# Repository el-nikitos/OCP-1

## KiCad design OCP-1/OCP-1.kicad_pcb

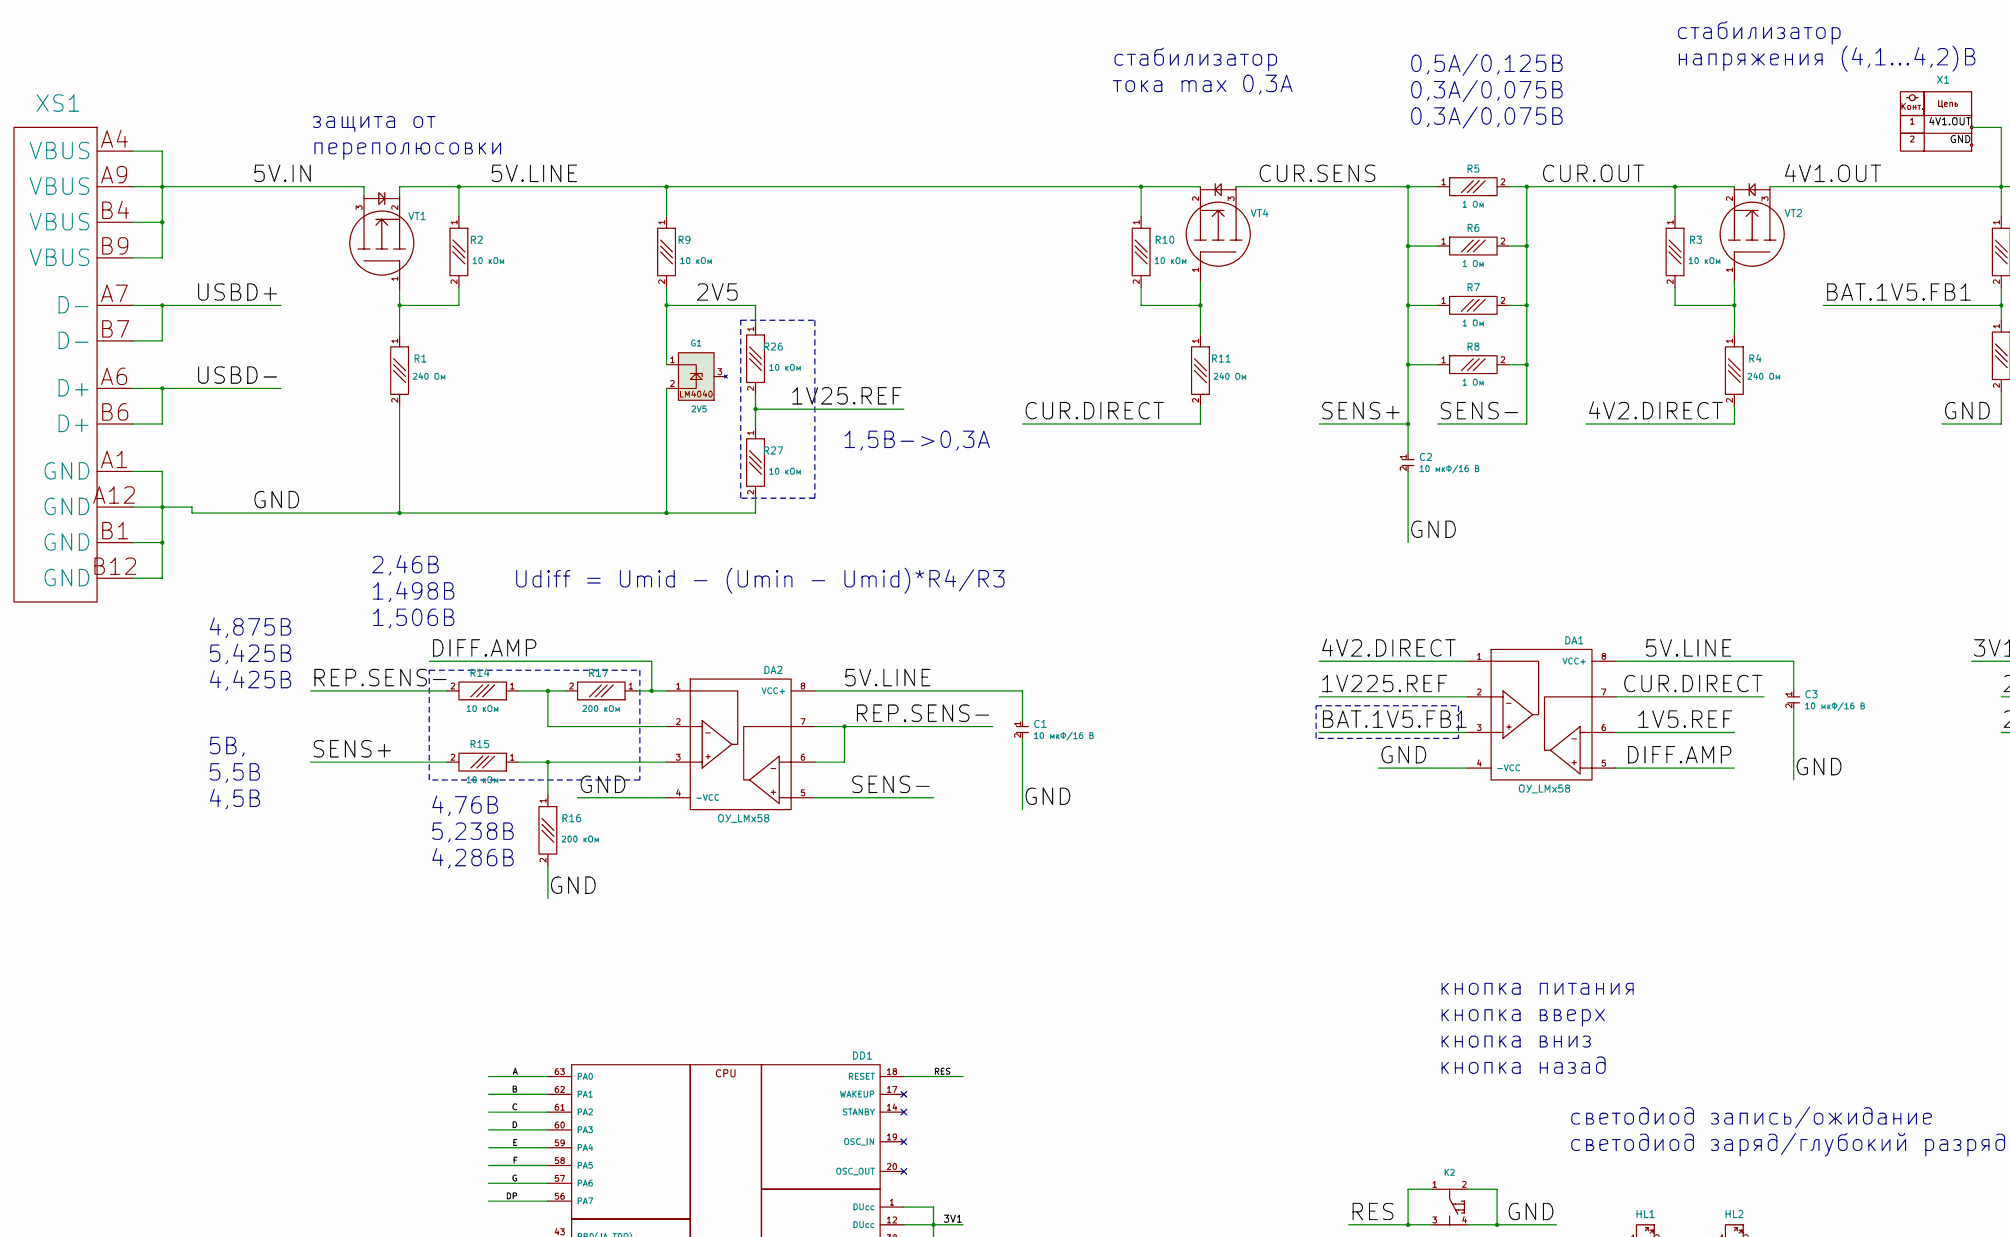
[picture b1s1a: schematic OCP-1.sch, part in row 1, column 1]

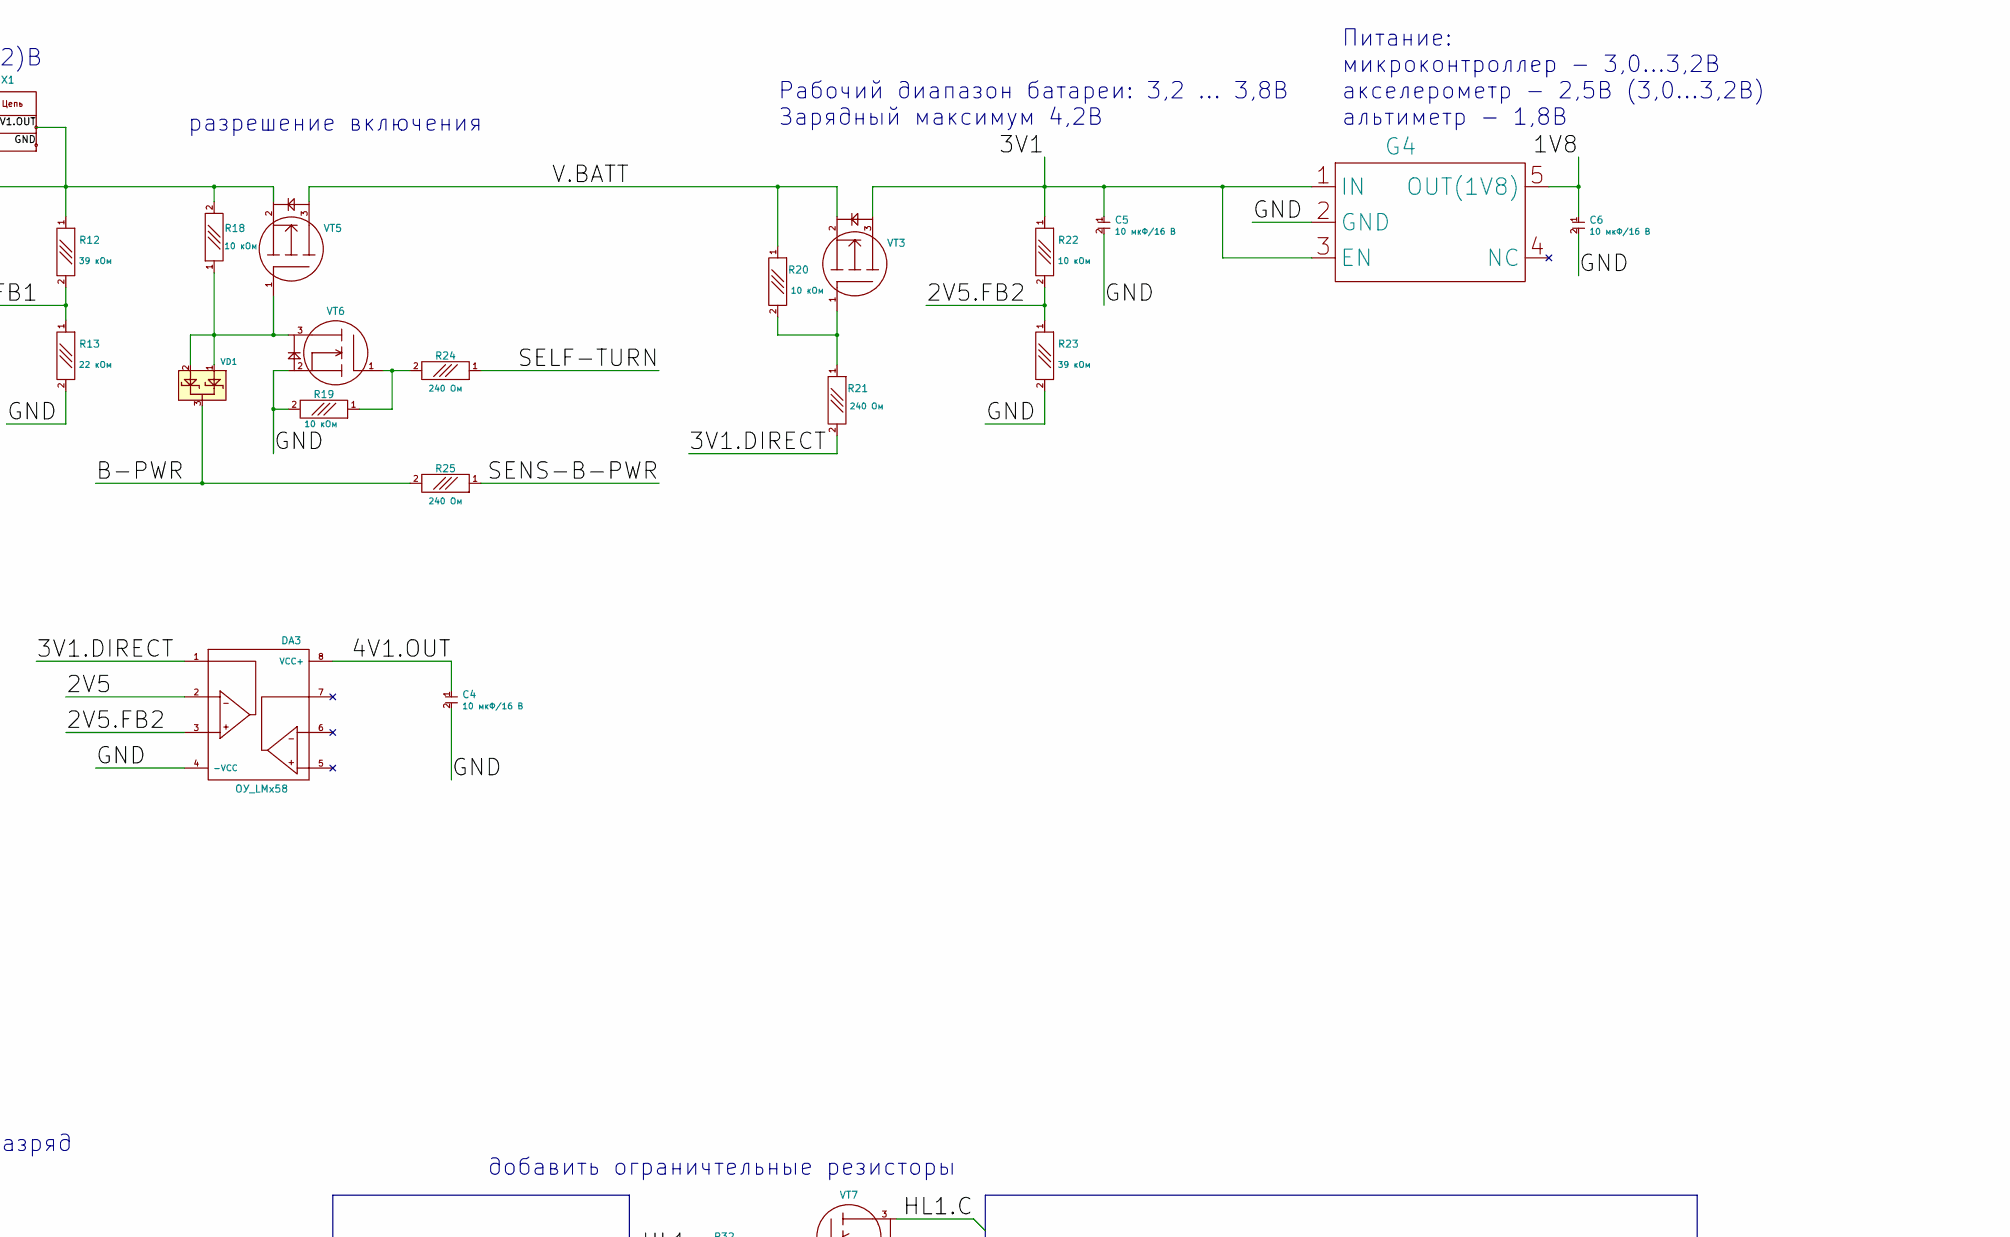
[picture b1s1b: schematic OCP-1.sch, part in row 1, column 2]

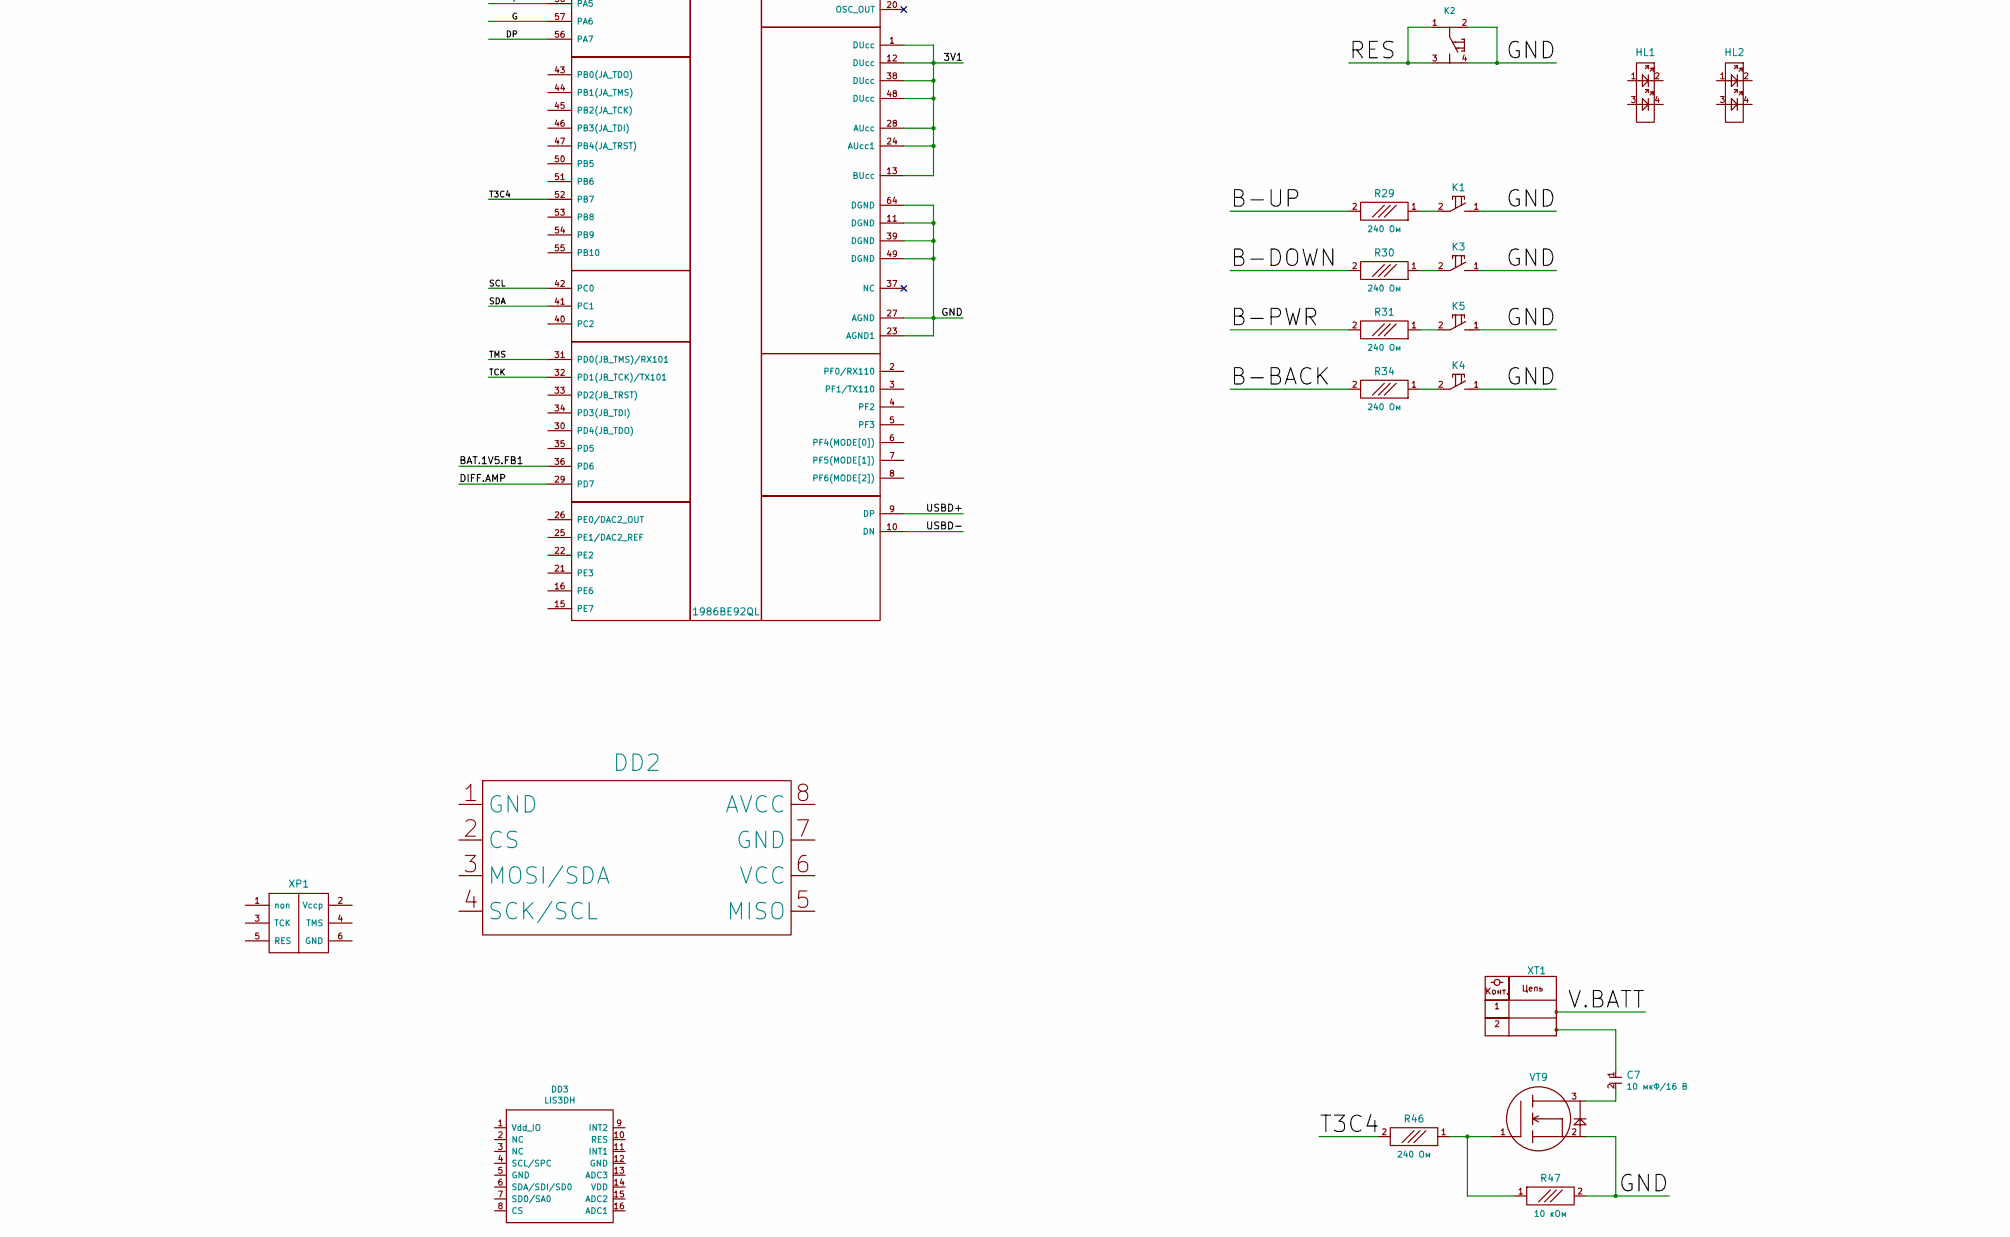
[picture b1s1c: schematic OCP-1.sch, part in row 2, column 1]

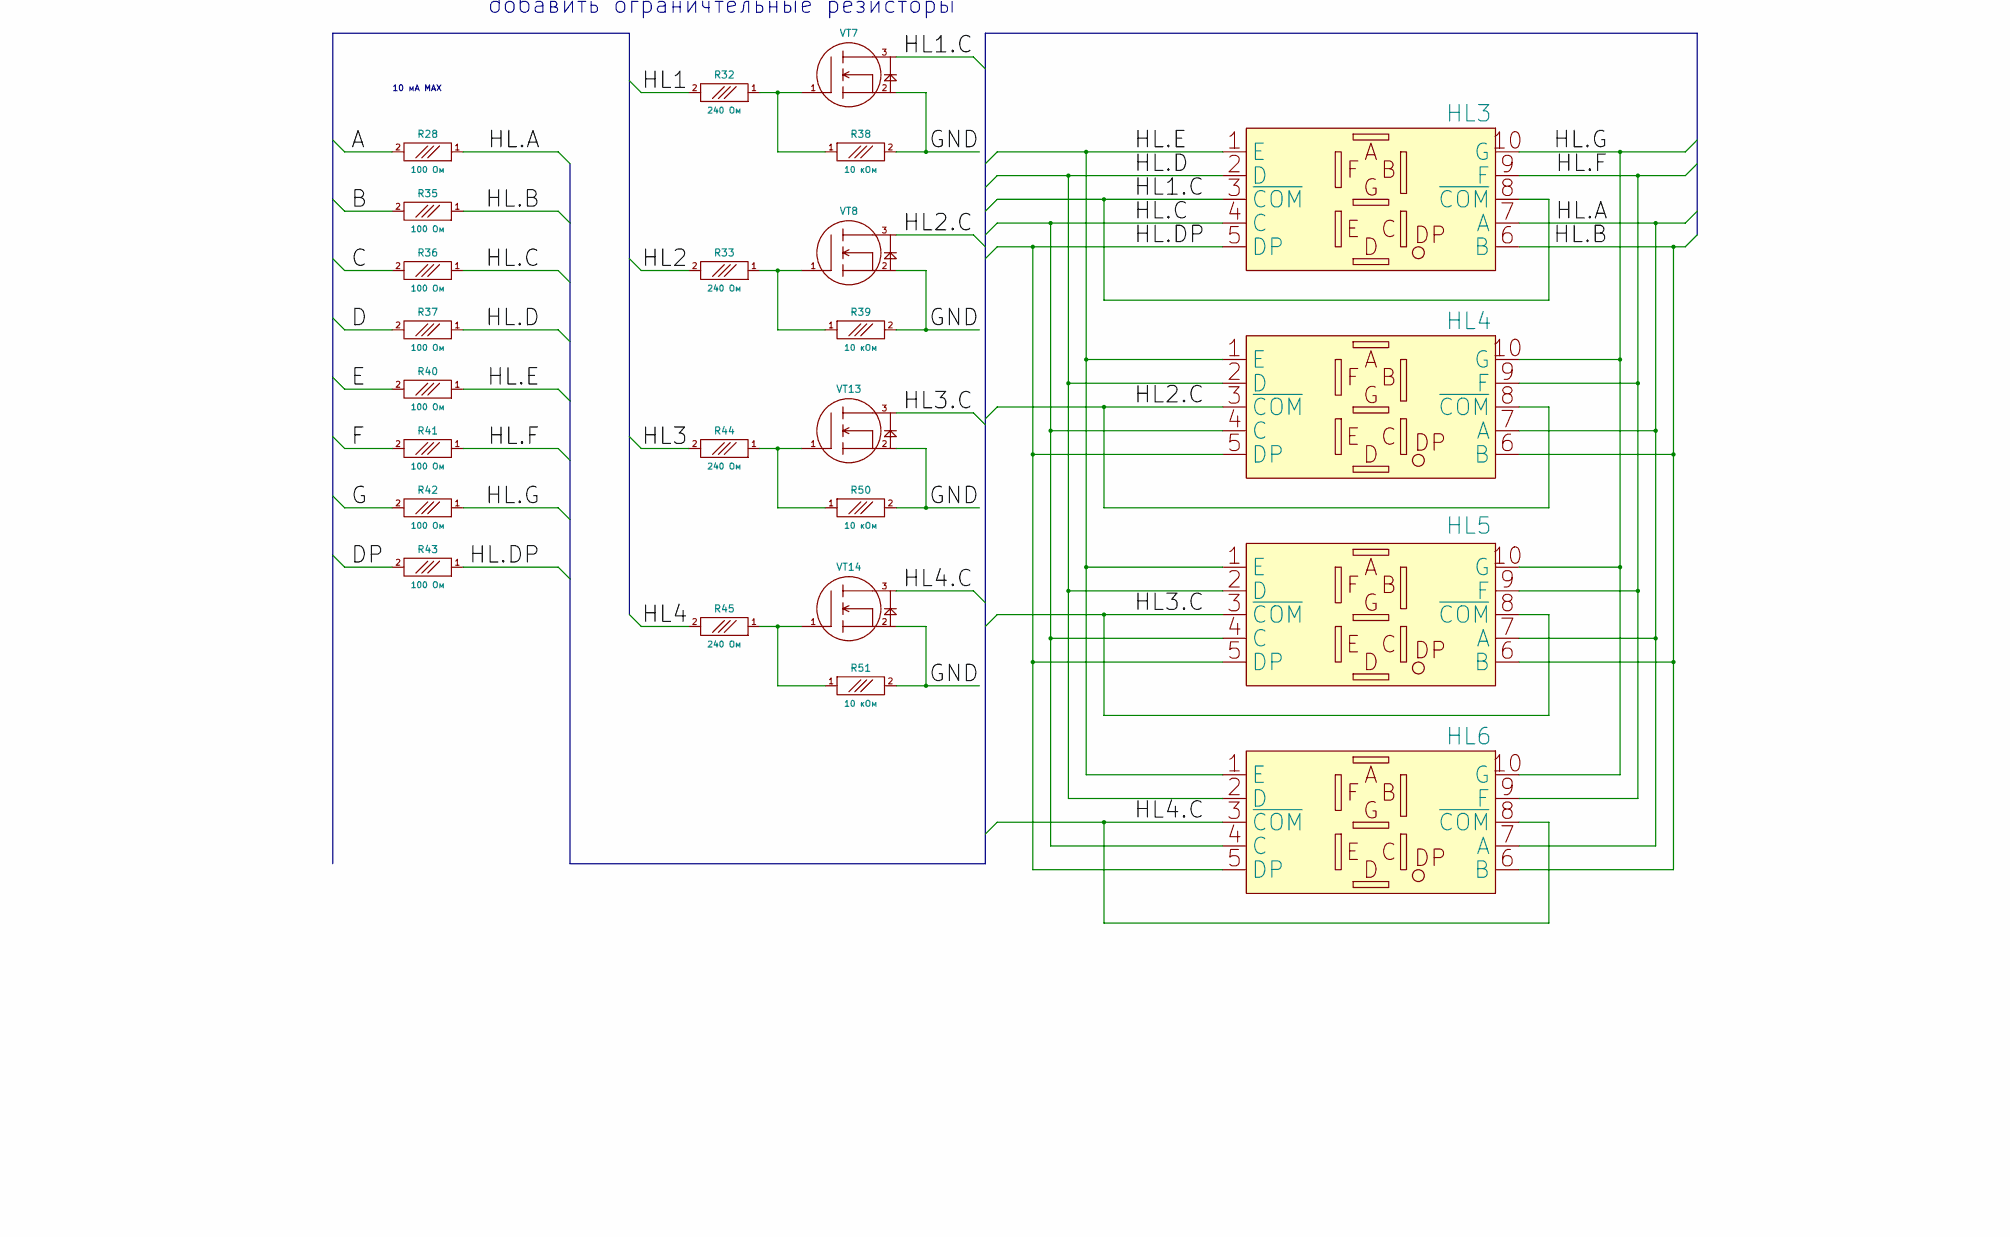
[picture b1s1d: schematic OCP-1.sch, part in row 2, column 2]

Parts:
C1, C2, C3, C4, C5, C6, C7: Конденсатор_керамический; Конденсатор_SMD_IEC_0805
DA1, DA2, DA3: ОУ_LMx58; SO-8
DD1: 1986ВЕ92QL; Микросхема_1986ВЕ92QL
DD2: BMP280
DD3: LIS3DH; акселерометр_LIS3DH
G1: ИОП_LM4040BIM3-2.5_NOPB; Корпус_КТ-46
G4: LDO_TPS76318DBVT; Преобразователь_LM2703_SOT-23-5
HL1, HL2: Светодиод_сдвоенный_KPB-3025SURKCGKC; Светодиод_SMD_m3025
HL3, HL4, HL5, HL6: Индикатор_7сегм_TOS-F2101AMG; LED-7SEGM-10x6,9
K1, K3, K4, K5: кнопка; Кнопка_FSMSM
K2: Кнопка_KLS7-TS5401-1.35-250-T; Кнопка_KLS7-TS5401
R1, R2, R3, R4, R5, R6, R7, R8, R9, R10, R11, R12, R13, R14, R15, R16, R17, R18, R19, R20, R21, R22, R23, R24, R25, R26, R27, R28, R29, R30, R31, R32, R33, R34, R35, R36, R37, R38, R39, R40, R41, R42, R43, R44, R45, R46, R47, R50, R51: Резистор_0,065Вт; Резистор_SMD_0603_0,065_Вт
VD1: Диоды_шоттки_BAR43CFILM; Транзистор_IRLML6344TR_SOT-23
VT1, VT2, VT3, VT4, VT5: Транзистор_полевой_P-канал(IRLML2246TRPBF); Транзистор_IRLML6344TR_SOT-23
VT6, VT7, VT8, VT9, VT13, VT14: Транзистор_полевой_N-канальный_КП526А9; Корпус_КТ-46
X1: Клеммник_х2; Клеммник_х2_шаг2.54
XP1: СНП346-6ВП_(отладочная); Вилка_СНП346_6
XS1: UBS-type-C-105450-0101&упрощенная; usb-type-c
XТ1: Клеммник_х2; Клеммник_х2_шаг2.54

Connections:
/1V5.REF: DA1.6
/1V8: C6.1, G4.5 (OUT(1V8))
/1V25.REF: R26.2, R27.1
/1V225.REF: DA1.2
/2V5: DA3.2, G1.1, R9.2, R26.1
/2V5.FB2: DA3.3, R22.2, R23.1
/3V1: C5.1, DD1.1 (DUcc), DD1.12 (DUcc), DD1.13 (BUcc), DD1.24 (AUcc1), DD1.28 (AUcc), DD1.38 (DUcc), DD1.48 (DUcc), G4.1 (IN), G4.3 (EN), R22.1, VT3.3
/3V1.DIRECT: DA3.1, R21.2
/4V1.OUT: C4.1, DA3.8 (VCC+), R12.1, R18.2, VT2.3, VT5.2, X1.1
/4V2.DIRECT: DA1.1, R4.2
/5V.IN: VT1.3, XS1.A4 (VBUS), XS1.A9 (VBUS), XS1.B4 (VBUS), XS1.B9 (VBUS)
/5V.LINE: C1.1, C3.1, DA1.8 (VCC+), DA2.8 (VCC+), R2.1, R9.1, R10.1, VT1.2, VT4.2
/A: DD1.63 (PA0), R28.2
/B: DD1.62 (PA1), R35.2
/B-BACK: R34.2
/B-DOWN: R30.2
/B-PWR: R25.2, R31.2, VD1.3
/B-UP: R29.2
/BAT.1V5.FB1: DA1.3, DD1.36 (PD6), R12.2, R13.1
/C: DD1.61 (PA2), R36.2
/CUR.DIRECT: DA1.7, R11.2
/CUR.OUT: DA2.5, R3.1, R5.2, R6.2, R7.2, R8.2, VT2.2
/CUR.SENS: C2.1, R5.1, R6.1, R7.1, R8.1, R15.2, VT4.3
/D: DD1.60 (PA3), R37.2
/DIFF.AMP: DA1.5, DA2.1, DD1.29 (PD7), R17.1
/DP: DD1.56 (PA7), R43.2
/E: DD1.59 (PA4), R40.2
/F: DD1.58 (PA5), R41.2
/G: DD1.57 (PA6), R42.2
/GND: C1.2, C2.2, C3.2, C4.2, C5.2, C6.2, DA1.4 (-VCC), DA2.4 (-VCC), DA3.4 (-VCC), DD1.11 (DGND), DD1.23 (AGND1), DD1.27 (AGND), DD1.39 (DGND), DD1.49 (DGND), DD1.64 (DGND), G1.2, G4.2 (GND), K1.1, K2.2, K2.4, K3.1, K4.1, K5.1, R1.2, R13.2, R16.2, R19.2, R23.2, R27.2, R38.2, R39.2, R47.2, R50.2, R51.2, VT6.2, VT7.2, VT8.2, VT9.2, VT13.2, VT14.2, X1.2, XS1.A1 (GND), XS1.A12 (GND), XS1.B1 (GND), XS1.B12 (GND)
/HL1: R32.2
/HL1.C: HL3.3 (~COM), HL3.8 (~COM), VT7.3
/HL2: R33.2
/HL2.C: HL4.3 (~COM), HL4.8 (~COM), VT8.3
/HL3: R44.2
/HL3.C: HL5.3 (~COM), HL5.8 (~COM), VT13.3
/HL4: R45.2
/HL4.C: HL6.3 (~COM), HL6.8 (~COM), VT14.3
/HL.A: HL3.7 (A), HL4.7 (A), HL5.7 (A), HL6.7 (A), R28.1
/HL.B: HL3.6 (B), HL4.6 (B), HL5.6 (B), HL6.6 (B), R35.1
/HL.C: HL3.4 (C), HL4.4 (C), HL5.4 (C), HL6.4 (C), R36.1
/HL.D: HL3.2 (D), HL4.2 (D), HL5.2 (D), HL6.2 (D), R37.1
/HL.DP: HL3.5 (DP), HL4.5 (DP), HL5.5 (DP), HL6.5 (DP), R43.1
/HL.E: HL3.1 (E), HL4.1 (E), HL5.1 (E), HL6.1 (E), R40.1
/HL.F: HL3.9 (F), HL4.9 (F), HL5.9 (F), HL6.9 (F), R41.1
/HL.G: HL3.10 (G), HL4.10 (G), HL5.10 (G), HL6.10 (G), R42.1
/REP.SENS-: DA2.6, DA2.7, R14.2
/RES: DD1.18 (RESET), K2.1, K2.3
/SCL: DD1.42 (PC0)
/SDA: DD1.41 (PC1)
/SELF-TURN: R24.1
/SENS-B-PWR: R25.1
/T3C4: DD1.52 (PB7), R46.2
/TCK: DD1.32 (PD1(JB_TCK)/TX101)
/TMS: DD1.31 (PD0(JB_TMS)/RX101)
/USBD+: DD1.9 (DP), XS1.A7 (D-), XS1.B7 (D-)
/USBD-: DD1.10 (DN), XS1.A6 (D+), XS1.B6 (D+)
/V.BATT: R20.1, VT3.2, VT5.3, XТ1.1
unnamed: C7.1, XТ1.2
unnamed: C7.2, VT9.3
unnamed: DA2.2, R14.1, R17.2
unnamed: DA2.3, R15.1, R16.1
unnamed: K1.2, R29.1
unnamed: K3.2, R30.1
unnamed: K4.2, R34.1
unnamed: K5.2, R31.1
unnamed: R1.1, R2.2, VT1.1
unnamed: R3.2, R4.1, VT2.1
unnamed: R10.2, R11.1, VT4.1
unnamed: R18.1, VD1.1, VD1.2, VT5.1, VT6.3
unnamed: R19.1, R24.2, VT6.1
unnamed: R20.2, R21.1, VT3.1
unnamed: R32.1, R38.1, VT7.1
unnamed: R33.1, R39.1, VT8.1
unnamed: R44.1, R50.1, VT13.1
unnamed: R45.1, R51.1, VT14.1
unnamed: R46.1, R47.1, VT9.1

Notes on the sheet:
защита от переполюсовки
кнопка питания кнопка вверх кнопка вниз кнопка назад
светодиод запись/ожидание светодиод заряд/глубокий разряд
стабилизатор напряжения (4,1…4,2)В
5В, 5,5В 4,5В
4,875В 5,425В 4,425В
0,5А/0,125В 0,3А/0,075В 0,3А/0,075В
4,76В 5,238В 4,286В
Udiff = Umid - (Umin - Umid)*R4/R3
2,46В 1,498В 1,506В
1,5В->0,3А
стабилизатор тока max 0,3А
Питание: микроконтроллер - 3,0...3,2В акселерометр - 2,5В (3,0...3,2В) альтиметр - 1,8В
Рабочий диапазон батареи: 3,2 ... 3,8В Зарядный максимум 4,2В
разрешение включения
10 мА MAX
добавить ограничтельные резисторы

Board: 2 copper layers, 91 parts (0 on the bottom side), 62 nets, no tracks yet.

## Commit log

2021-05-30 схема питания 220В-5В и его обвес
2021-06-25 изменен ac-dc и дублирующий контроллер на esp32
2021-10-06 теперь это альтиметр со звуковым оповещением
2021-10-08 схема заряда аккумулятора и требования к питанию периферии
2021-10-10 схема питания МК и датчиков
2021-10-31 добавлена схема включения и расположение индикаторов
2021-10-31 заготовка usb-type-c
2021-11-06 определена схема индикаторов, динамика, не исправлены резисторы питания
